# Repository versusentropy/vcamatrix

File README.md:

## eurorack 4x4 VCA matrix

revision v3.1
license CC-BY-SA-NC 4.0

46hp
355mA/325mA +/-12V

* signal input
  * full eurorack level (TODO scope pic)
  * passive normalized to input above
  * switch per column to normalize row 3&4 to 1&2 like a stereo pair
* 0-5V CV linear control
  * normalized to the CV above 
  * pre-/post knob switch between rows 1→2 and 3→4 
    * for stereo or main & send-fx 
    * 2→3 fixed pre
* dedicated output for each VCA
* mix output per VCA, that sums to the right, if nothing is plugged in
  * pin-headers on the back to chain multiple modules

Nobody ane would try to assemble the SMT parts by hand.
All SMT have a LCSC column for JLCPCB. For resistors all thin-film resistors <1% with the same package should be fine.  

## THT parts assembly

### BOM

* 1x 2x5 2.54mm shrouded pin header
  * power connector
* 2x 667-EEU-FR1V680H
  * electrolytic THT capacitor at power input (CP_Radial_D6.3mm_P2.50mm) 
* 1x 5k Trimmer 
  * Mouser 652-3296W-1-502LF
* 8x 2pin 2.54mm pin header
* 16x LED
  * Mouser 696-SSL-LX3044LYD
  * red version of same LED might work
  * other LEDs will most likely need different resistors.
* 8x Sub-Miniature Switch SPDT
* 4x Sub-Miniature DPDT

### Steps

**I recommend to do it EXACTLY 100% IN THIS ORDER WITHOUT COMBINING OR SKIPPING ANY STEPS.** 
I tried different processes. Many come with unexpected annoyances or take much longer without benefit. 
Place jacks means place jacks and nothing else!

#### 1
Place and solder 2.54mm pin headers at a right angle flush to the PCB. Solder 1pin, check & fix, finish.

* 4x 2pin 2.54mm pin header (green)
  * **These can not be installed later**, because the jacks will block the other side!
* 4x 2pin 2.54mm pin header (red)
  * These could be soldered to a finished module. But I recommend to solder them, even if you don't want to chain multiple modules. They help with placing jacks by holding up the PCB.

#### 2
Place and solder the power header

* 2x5 2.54mm shrouded pin header
  * **the notch must match the marking on the PCB!**
  * flush to the pcb to prevent damage when plugging in
    * solder 1pin, check & fix, finish

#### 3

Place and solder the offset trimmer

* 5k 3296W-1-502LF Trimmer
  * flush to the pcb to prevent damage when calibrating
    * solder 1pin, check & fix, finish

#### 4

Place all jacks. The loose leg goes into the square hole. Put it in first, then the next pin. Then third pin should go in easily. 
It's no problem, if 2 loose legs from the square pads of a neighboring jacks touch on the back, because that is the GND pin. Jacks are placed such, that the GND pads of 2 adjacent jacks always pair up.

#### 5

**Read the whole step, then** put on the front panel screw the 4 jacks at the corners and the 2 in the middle (5V and ∑) **FLUSH TO THE PANEL**.

 * Once the panel is put on, 
 * before and after screwing jacks in, 
 * until they have been soldered,
   * The panel
   * or the pcb
     * will tilt down on the side of the pots and rip out a few jacks.
     * then you have to remove the panel, which will pull out more jacks.
       * and you have to start over
         * that's why **YOU MUST NOT STOP HOLDING THE PCB AND THE PANEL TOGETHER UNTIL YOU ARE DONE!**
         * once the screws are tightened **JACK FLUSH TO THE PANEL**, flip everything into your positon for soldering
           * **WHILE HOLDING EVERYTHING TOGETHER!** put some weight near the ∑ to keep everything together.
 * **EVEN ONCE ALL JACKS ARE SOLDERED** 
   * **YOU MUST NOT REST YOU HAND** 
   * **OR PUT ANYTHING ELSE**
     * **ON THE POTS' SIDE OF**
       * **THE PCB**
       * **OR THE PANEL**
         * until much later, when the pots are placed
           * **OR YOU RISK TO BEND AND DAMAGE THE PCB**!
 * solder jacks with screws **while pressing the pcb down until the solder hardened! Do not proceed, if a jack isn't flush with the pcb.**
   * start with ∑
   * then 5V
   * then the 4 corners
 * now the risk of pulling out jacks is gone. 
 * **KEEP BEING CAREFUL NOT TO BEND THE PCB. DO NOT PUT PRESSURE ON EITHER SIDE WHERE THE POTS ARE MISSING!**

#### 6
 * verify, that all jacks sit flush with the pcb and the panel.
 * only then solder all remaining jacks
   * be careful not to solder one of the empty holes for the switches in the middle row by accident.
   * work from jack by jack and only solder a jack, if all 3 pins are properly inserted. Single improperly placed jacks should be soldered with the pots later.
 * verify, that all jacks sit flush with the pcb and the panel.
 * unscrew and remove panel

#### 7

Place and solder capacitors next to the power header.

* 2x 667-EEU-FR1V680H

#### 8

Place on the front side

 * 16x Pots
   * no metal tab at the pot
   * 1 washer
 * 4x DPDT switch between jacks
   * with 1 screw
   * all switches in same position (because it's easier to get the panel on)
 * 8x SPDT switch between pots
   * with 1 screw
   * all switches in same position (because it's easier to get the panel on)

#### 9
Place pcb on a box like in the photo, so LEDs' legs can dangle below.
 * 16x LED
   * Long leg into round hole
   * Must not stick out above the panel, until the panel is screwed to the other parts!

#### 10
Putting on the panel is a bit tricky. Do not use any force!
Panel and pcb should stay close to parallel, but getting in the switches needs some tilting.  

* LEDs should be out of the way at the bottom
* **do not tilt or bump, until all switches are through their holes**
  * or the switches fall over
    * and you might have to start over
* pots go first
  * if pcb and panel are at an angle, they won't go in easily. pulling the stuck panel back can pull a pot from the pcb. 
    * and you might have to start over 
* switches
  * one by one, from one end to the other
    * lowering the panel at a very slight angle
  * use tweezers to help them in
    * don't tip them over

#### 11

 * Verify pcb and panel are parallel
 * Screw all jacks flush
   * careful not to bend the pcb. pots should move in place
 * Verify pcb and panel are parallel
 * Screw pots flush to the panel
   * pot should lift slightly from the pcb (its pins will still stick out properly)
   * MAKE SURE NOT TO BEND THE PCB, when a pot sits a bit tight with its pins.
     * do others first
     * wiggle
 * Verify pcb and panel are parallel
 * Turn over for soldering without losing the LEDs
 * Solder pots
 * Screw switches flush to the panel
   * pins should barely stick out.

 * Turn over for soldering
 * Move LEDs into holes
 * Solder switches
   * make sure to heat pad and pin even, if the pin barely sticks out
 * Solder LEDs one by one while module is (close to) vertical
   * adjust LED to panel 
   * solder short leg first
   * check alignment
   * grab front and long leg with one hand
   * reheat round pad and adjust
   * solder 2nd pin and cut legs

#### 12

To check for shorts before powering up measure across the small SMT capacitors near the power header, that are connected to the electrolytic caps via big copper planes.

* positive side
* negative side
* positive (+ of electrolytic) to negative (- of electrolytic)

Trimmer should be set such, that
* VCAs are fully closed when their knob is set fully counter-clockwise.
* when properly set, there should be no bleed.

TODO add scope pics

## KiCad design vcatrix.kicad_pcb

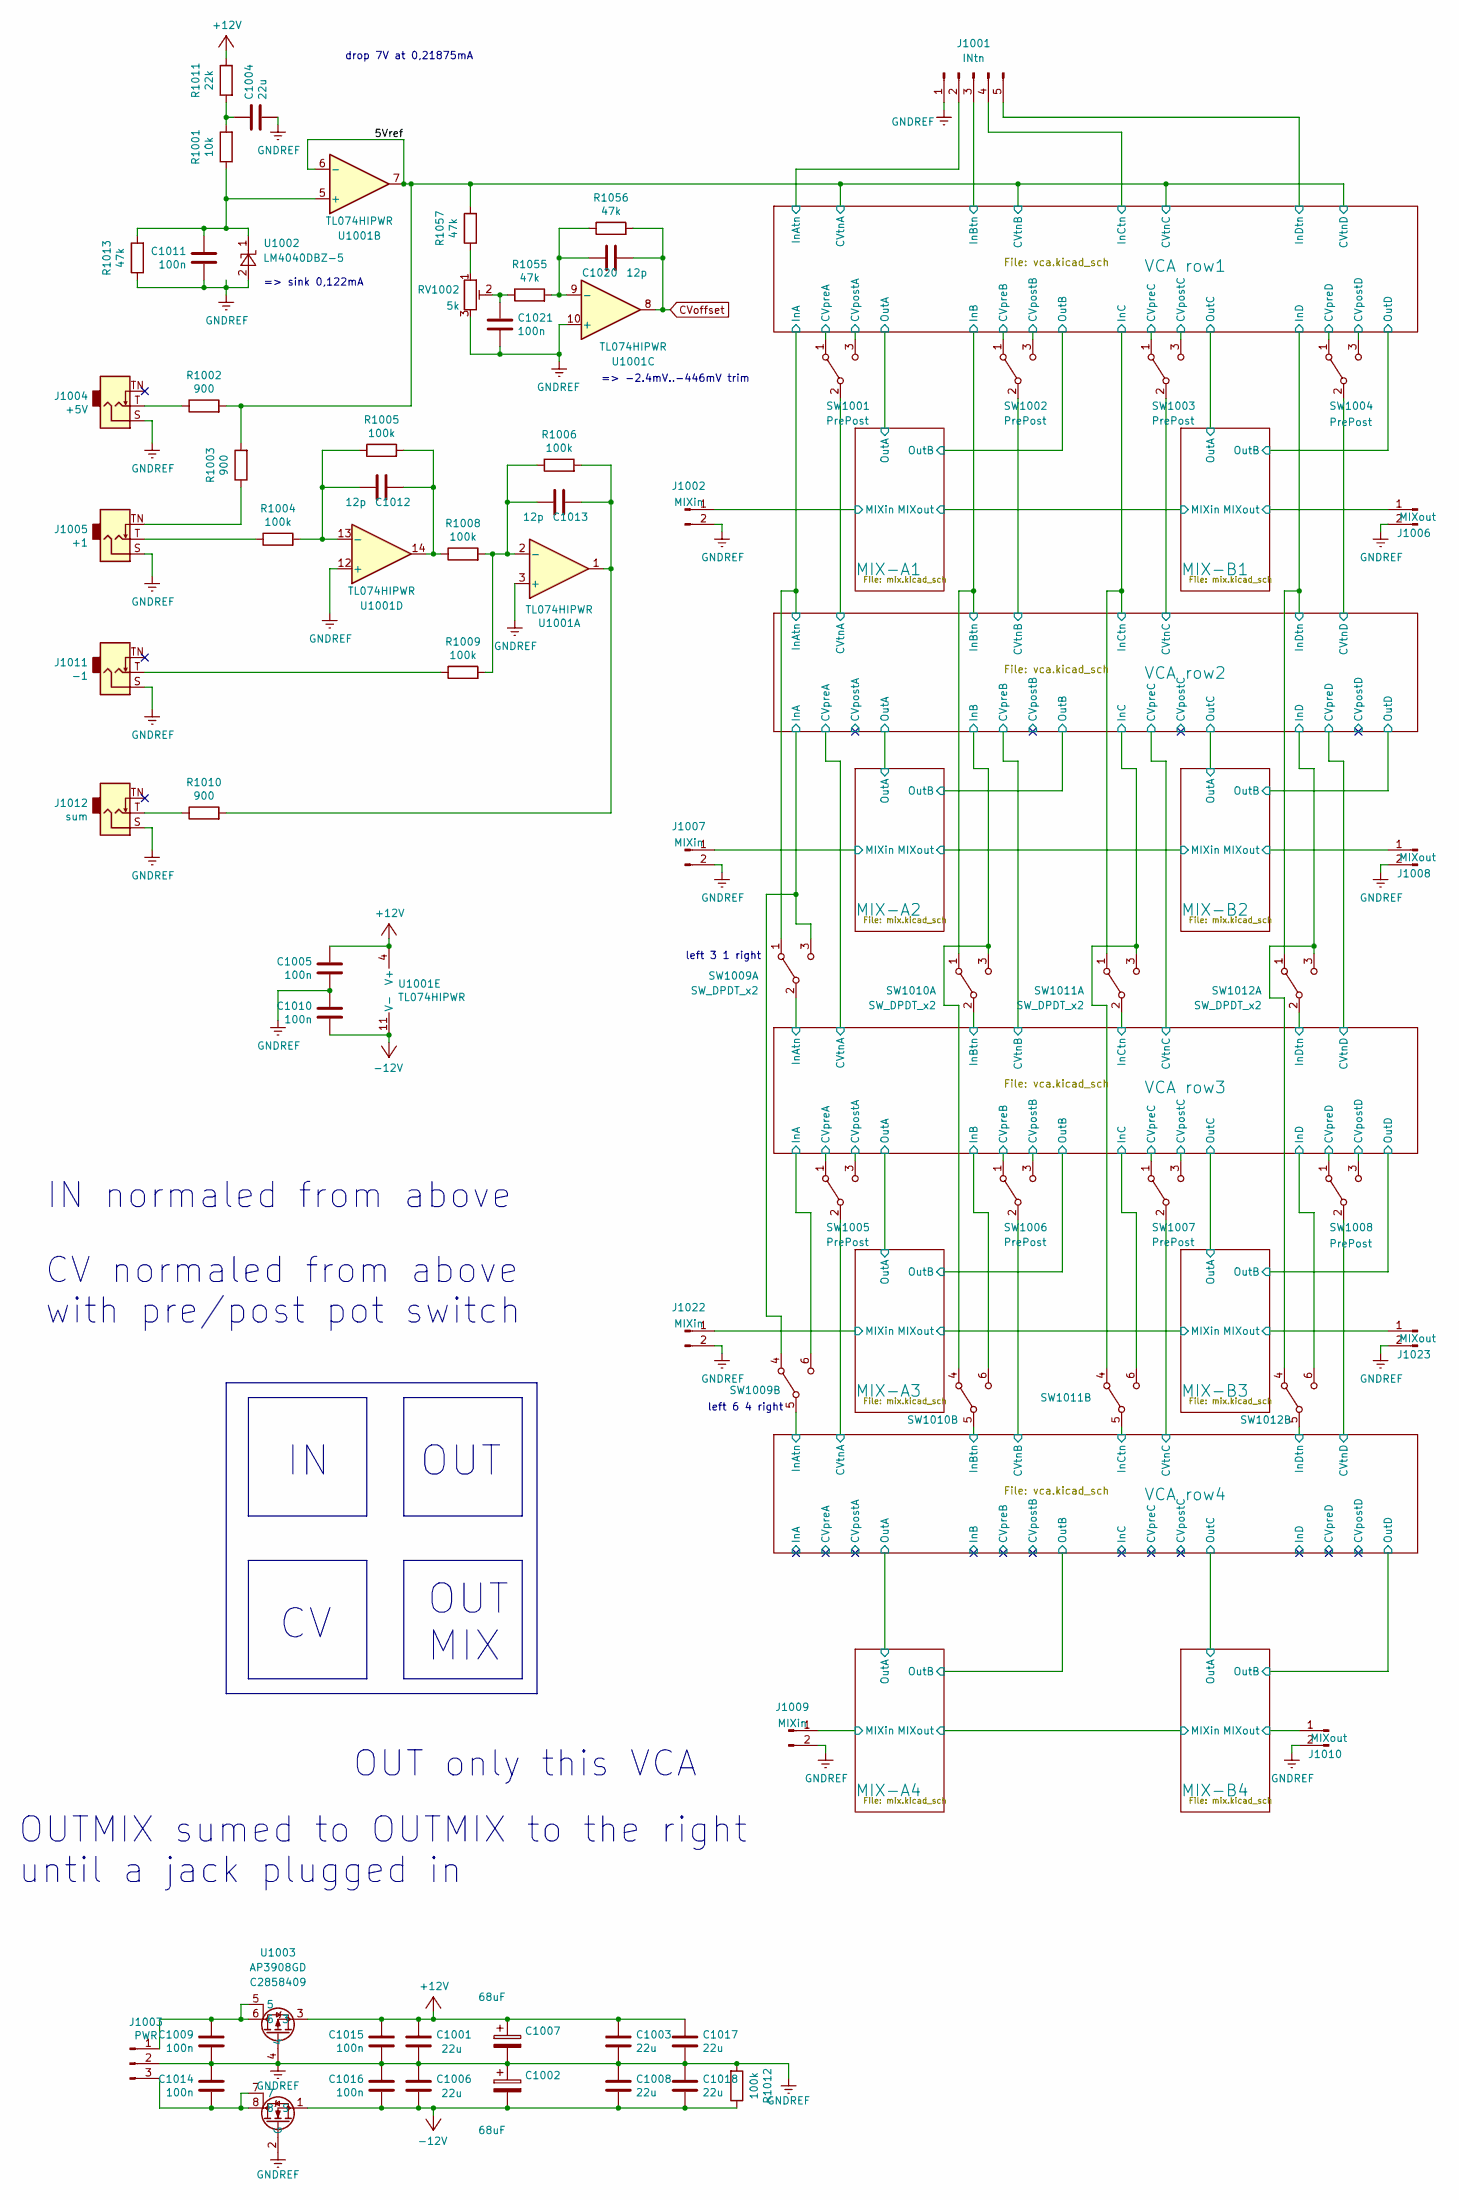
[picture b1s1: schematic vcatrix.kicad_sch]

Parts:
C1001, C1003, C1004, C1006, C1008, C1017, C1018: 22u; C_0805_2012Metric; LCSC C86816
C1002, C1007: 68uF; CP_Radial_D6.3mm_P2.50mm; Mouser 667-EEU-FR1V680H
C1005, C1009, C1010, C1011, C1014, C1015, C1016, C1021: 100n; C_0402_1005Metric; LCSC C307331
C1012, C1013, C1020: 12p; C_0402_1005Metric; LCSC C1547
J1001: INtn; PinHeader_1x05_P2.54mm_Vertical
J1002, J1007, J1009, J1022: MIXin; PinHeader_1x02_P2.54mm_Vertical
J1003: PWR; eurorac_power-v2; Mouser 737-BHR-10-VUA
J1004: +5V; Jack_3.5mm_QingPu_WQP-PJ398SM_Vertical_CircularHolesSMALL
J1005: +1; Jack_3.5mm_QingPu_WQP-PJ398SM_Vertical_CircularHolesSMALL
J1006, J1008, J1010, J1023: MIXout; PinHeader_1x02_P2.54mm_Vertical
J1011: -1; Jack_3.5mm_QingPu_WQP-PJ398SM_Vertical_CircularHolesSMALL
J1012: sum; Jack_3.5mm_QingPu_WQP-PJ398SM_Vertical_CircularHolesSMALL
R1001: 10k; R_0402_1005Metric; LCSC C190095
R1002, R1003, R1010: 900; R_0603_1608Metric; LCSC C3013565
R1004, R1005, R1006, R1008, R1009, R1012: 100k; R_0402_1005Metric; LCSC C317929
R1011: 22k; R_0402_1005Metric; LCSC C25768
R1013, R1055, R1056, R1057: 47k; R_0402_1005Metric; LCSC C358418
RV1002: 5k; Potentiometer_Bourns_3296W_Vertical; Mouser 652-3296W-1-502LF
SW1001, SW1002, SW1003, SW1004, SW1005, SW1006, SW1007, SW1008: PrePost; SW_SPDT_2_5mm
SW1009, SW1010, SW1011, SW1012: SW_DPDT_x2; SW_DPDT_2_5mm
U1001: TL074HIPWR; TSSOP-14_4.4x5mm_P0.65mm; LCSC C4370424
U1002: LM4040DBZ-5; SOT-23; LCSC C460606
U1003: AP3908GD; LCSC C2858409

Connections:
+12V: C1001.1, C1003.1, C1005.2, C1007.1, C1015.2, C1017.1, R1011.1, U1001.4 (V+), U1003.3; also elsewhere on the board
-12V: C1002.2, C1006.2, C1008.2, C1010.1, C1016.1, C1018.2, R1012.1, U1001.11 (V-), U1003.1 (S); also elsewhere on the board
/5Vref: R1002.2, R1003.2, R1057.2, U1001.6 (-), U1001.7; also elsewhere on the board
/MIX-A1/MIXin: J1002.1; also elsewhere on the board
/MIX-A2/MIXin: J1007.1; also elsewhere on the board
/MIX-A3/MIXin: J1022.1; also elsewhere on the board
/MIX-A4/MIXin: J1009.1; also elsewhere on the board
/MIX-B1/MIXout: J1006.1; also elsewhere on the board
/MIX-B2/MIXout: J1008.1; also elsewhere on the board
/MIX-B3/MIXout: J1023.1; also elsewhere on the board
/MIX-B4/MIXout: J1010.1; also elsewhere on the board
/VCA row1/CVpostA: SW1001.3 (C); also elsewhere on the board
/VCA row1/CVpostB: SW1002.3 (C); also elsewhere on the board
/VCA row1/CVpostC: SW1003.3 (C); also elsewhere on the board
/VCA row1/CVpostD: SW1004.3 (C); also elsewhere on the board
/VCA row1/CVpreA: SW1001.1 (A); also elsewhere on the board
/VCA row1/CVpreB: SW1002.1 (A); also elsewhere on the board
/VCA row1/CVpreC: SW1003.1 (A); also elsewhere on the board
/VCA row1/CVpreD: SW1004.1 (A); also elsewhere on the board
/VCA row1/InA: SW1009.1 (A); also elsewhere on the board
/VCA row1/InAtn: J1001.2; also elsewhere on the board
/VCA row1/InB: SW1010.1 (A); also elsewhere on the board
/VCA row1/InBtn: J1001.3; also elsewhere on the board
/VCA row1/InC: SW1011.1 (A); also elsewhere on the board
/VCA row1/InCtn: J1001.4; also elsewhere on the board
/VCA row1/InD: SW1012.1 (A); also elsewhere on the board
/VCA row1/InDtn: J1001.5; also elsewhere on the board
/VCA row2/CVtnA: SW1001.2 (B); also elsewhere on the board
/VCA row2/CVtnB: SW1002.2 (B); also elsewhere on the board
/VCA row2/CVtnC: SW1003.2 (B); also elsewhere on the board
/VCA row2/CVtnD: SW1004.2 (B); also elsewhere on the board
/VCA row2/InA: SW1009.3 (C), SW1009.4 (A); also elsewhere on the board
/VCA row2/InB: SW1010.3 (C), SW1010.4 (A); also elsewhere on the board
/VCA row2/InC: SW1011.3 (C), SW1011.4 (A); also elsewhere on the board
/VCA row2/InD: SW1012.3 (C), SW1012.4 (A); also elsewhere on the board
/VCA row3/CVpostA: SW1005.3 (C); also elsewhere on the board
/VCA row3/CVpostB: SW1006.3 (C); also elsewhere on the board
/VCA row3/CVpostC: SW1007.3 (C); also elsewhere on the board
/VCA row3/CVpostD: SW1008.3 (C); also elsewhere on the board
/VCA row3/CVpreA: SW1005.1 (A); also elsewhere on the board
/VCA row3/CVpreB: SW1006.1 (A); also elsewhere on the board
/VCA row3/CVpreC: SW1007.1 (A); also elsewhere on the board
/VCA row3/CVpreD: SW1008.1 (A); also elsewhere on the board
/VCA row3/InA: SW1009.6 (C); also elsewhere on the board
/VCA row3/InAtn: SW1009.2 (B); also elsewhere on the board
/VCA row3/InB: SW1010.6 (C); also elsewhere on the board
/VCA row3/InBtn: SW1010.2 (B); also elsewhere on the board
/VCA row3/InC: SW1011.6 (C); also elsewhere on the board
/VCA row3/InCtn: SW1011.2 (B); also elsewhere on the board
/VCA row3/InD: SW1012.6 (C); also elsewhere on the board
/VCA row3/InDtn: SW1012.2 (B); also elsewhere on the board
/VCA row4/CVtnA: SW1005.2 (B); also elsewhere on the board
/VCA row4/CVtnB: SW1006.2 (B); also elsewhere on the board
/VCA row4/CVtnC: SW1007.2 (B); also elsewhere on the board
/VCA row4/CVtnD: SW1008.2 (B); also elsewhere on the board
/VCA row4/InAtn: SW1009.5 (B); also elsewhere on the board
/VCA row4/InBtn: SW1010.5 (B); also elsewhere on the board
/VCA row4/InCtn: SW1011.5 (B); also elsewhere on the board
/VCA row4/InDtn: SW1012.5 (B); also elsewhere on the board
CVoffset: C1020.2, R1056.2, U1001.8; also elsewhere on the board
GNDREF: C1001.2, C1002.1, C1003.2, C1004.2, C1005.1, C1006.1, C1007.2, C1008.1, C1009.1, C1010.2, C1011.1, C1014.2, C1015.1, C1016.2, C1017.2, C1018.1, C1021.1, J1001.1, J1002.2, J1003.2, J1004.S, J1005.S, J1006.2, J1007.2, J1008.2, J1009.2, J1010.2, J1011.S, J1012.S, J1022.2, J1023.2, R1012.2, R1013.1, RV1002.3, U1001.3 (+), U1001.10 (+), U1001.12 (+), U1002.2 (A), U1003.2 (G), U1003.4; also elsewhere on the board
unnamed: C1004.1, R1001.2, R1011.2
unnamed: C1012.1, R1005.2, R1008.1, U1001.14
unnamed: C1013.1, R1006.2, R1010.2, U1001.1
unnamed: C1021.2, R1055.1, RV1002.2
unnamed: C1009.2, J1003.1, U1003.5, U1003.6
unnamed: C1014.1, J1003.3, U1003.7, U1003.8
unnamed: J1004.T, R1002.1
unnamed: J1005.T, R1004.1
unnamed: J1005.TN, R1003.1
unnamed: J1011.T, R1009.1
unnamed: J1012.T, R1010.1
unnamed: R1057.1, RV1002.1
unnamed: C1013.2, R1006.1, R1008.2, R1009.2, U1001.2 (-)
unnamed: C1011.2, R1001.1, R1013.2, U1001.5 (+), U1002.1 (K)
unnamed: C1020.1, R1055.2, R1056.1, U1001.9 (-)
unnamed: C1012.2, R1004.2, R1005.1, U1001.13 (-)

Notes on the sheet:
left 3 1 right
OUTMIX sumed to OUTMIX to the right until a jack plugged in
OUT only this VCA
CV normaled from above with pre/post pot switch
drop 7V at 0,21875mA
=> -2.4mV..-446mV trim
OUT MIX
left 6 4 right
OUT
IN normaled from above
=> sink 0,122mA

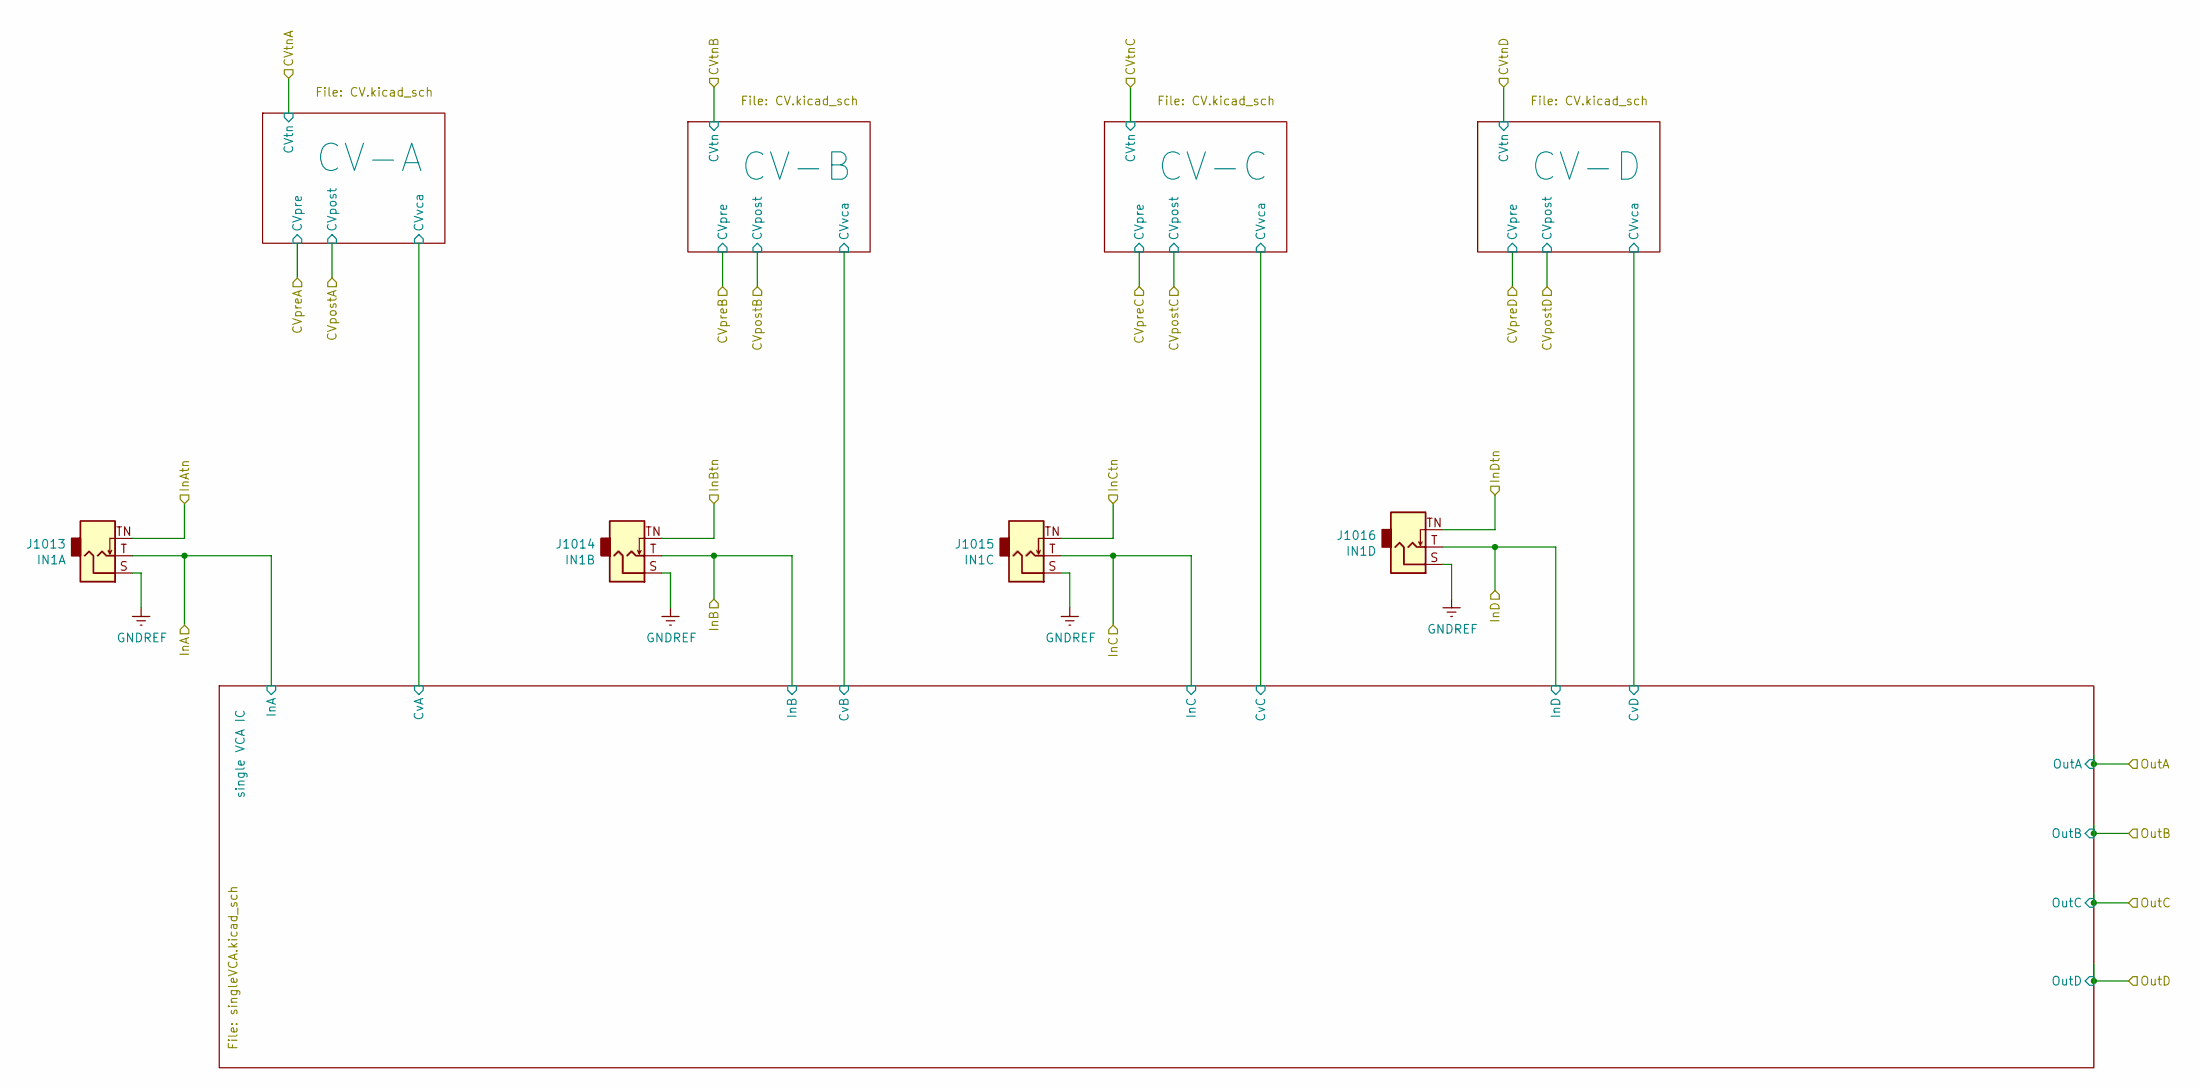
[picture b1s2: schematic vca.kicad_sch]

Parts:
J1013: IN1A; Jack_3.5mm_QingPu_WQP-PJ398SM_Vertical_CircularHolesSMALL
J1014: IN1B; Jack_3.5mm_QingPu_WQP-PJ398SM_Vertical_CircularHolesSMALL
J1015: IN1C; Jack_3.5mm_QingPu_WQP-PJ398SM_Vertical_CircularHolesSMALL
J1016: IN1D; Jack_3.5mm_QingPu_WQP-PJ398SM_Vertical_CircularHolesSMALL

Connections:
/VCA row1/InA: J1013.T; also elsewhere on the board
/VCA row1/InAtn: J1013.TN; also elsewhere on the board
/VCA row1/InB: J1014.T; also elsewhere on the board
/VCA row1/InBtn: J1014.TN; also elsewhere on the board
/VCA row1/InC: J1015.T; also elsewhere on the board
/VCA row1/InCtn: J1015.TN; also elsewhere on the board
/VCA row1/InD: J1016.T; also elsewhere on the board
/VCA row1/InDtn: J1016.TN; also elsewhere on the board
GNDREF: J1013.S, J1014.S, J1015.S, J1016.S; also elsewhere on the board

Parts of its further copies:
J2401, J3401, J4401: IN1D; Jack_3.5mm_QingPu_WQP-PJ398SM_Vertical_CircularHolesSMALL
J2402, J3402, J4402: IN1A; Jack_3.5mm_QingPu_WQP-PJ398SM_Vertical_CircularHolesSMALL
J2403, J3403, J4403: IN1B; Jack_3.5mm_QingPu_WQP-PJ398SM_Vertical_CircularHolesSMALL
J2404, J3404, J4404: IN1C; Jack_3.5mm_QingPu_WQP-PJ398SM_Vertical_CircularHolesSMALL

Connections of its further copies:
/VCA row1/InA: J2402.TN; also elsewhere on the board
/VCA row1/InB: J2403.TN; also elsewhere on the board
/VCA row1/InC: J2404.TN; also elsewhere on the board
/VCA row1/InD: J2401.TN; also elsewhere on the board
/VCA row2/InA: J2402.T; also elsewhere on the board
/VCA row2/InB: J2403.T; also elsewhere on the board
/VCA row2/InC: J2404.T; also elsewhere on the board
/VCA row2/InD: J2401.T; also elsewhere on the board
/VCA row3/InA: J3402.T; also elsewhere on the board
/VCA row3/InAtn: J3402.TN; also elsewhere on the board
/VCA row3/InB: J3403.T; also elsewhere on the board
/VCA row3/InBtn: J3403.TN; also elsewhere on the board
/VCA row3/InC: J3404.T; also elsewhere on the board
/VCA row3/InCtn: J3404.TN; also elsewhere on the board
/VCA row3/InD: J3401.T; also elsewhere on the board
/VCA row3/InDtn: J3401.TN; also elsewhere on the board
/VCA row4/InA: J4402.T; also elsewhere on the board
/VCA row4/InAtn: J4402.TN; also elsewhere on the board
/VCA row4/InB: J4403.T; also elsewhere on the board
/VCA row4/InBtn: J4403.TN; also elsewhere on the board
/VCA row4/InC: J4404.T; also elsewhere on the board
/VCA row4/InCtn: J4404.TN; also elsewhere on the board
/VCA row4/InD: J4401.T; also elsewhere on the board
/VCA row4/InDtn: J4401.TN; also elsewhere on the board
GNDREF: J2401.S, J2402.S, J2403.S, J2404.S, J3401.S, J3402.S, J3403.S, J3404.S, J4401.S, J4402.S, J4403.S, J4404.S; also elsewhere on the board

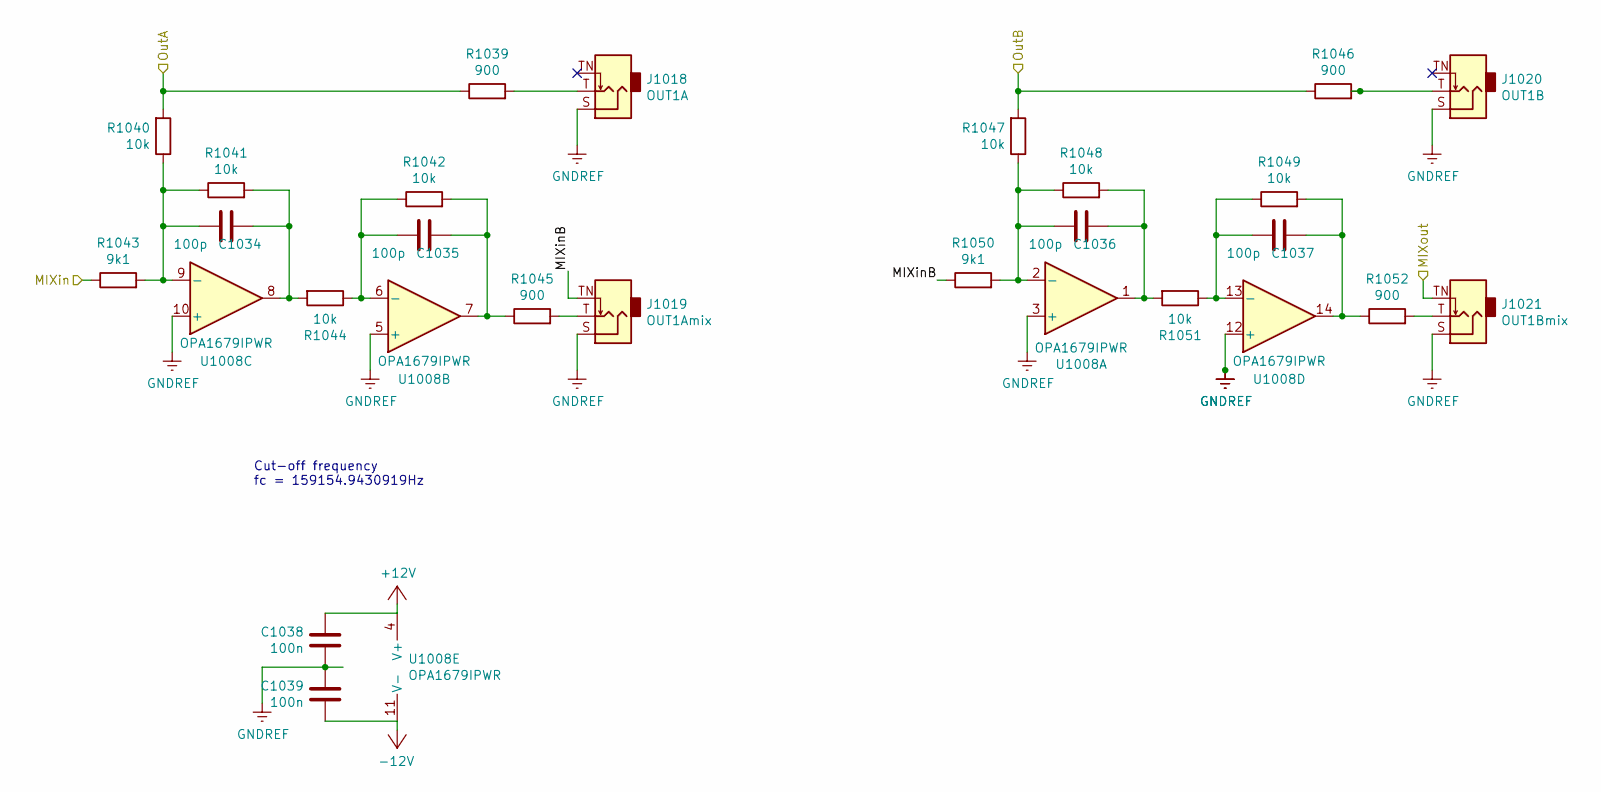
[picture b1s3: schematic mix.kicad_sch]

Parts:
C1034, C1035, C1036, C1037: 100p; C_0402_1005Metric; LCSC C1546
C1038, C1039: 100n; C_0402_1005Metric; LCSC C307331
J1018: OUT1A; Jack_3.5mm_QingPu_WQP-PJ398SM_Vertical_CircularHolesSMALL
J1019: OUT1Amix; Jack_3.5mm_QingPu_WQP-PJ398SM_Vertical_CircularHolesSMALL
J1020: OUT1B; Jack_3.5mm_QingPu_WQP-PJ398SM_Vertical_CircularHolesSMALL
J1021: OUT1Bmix; Jack_3.5mm_QingPu_WQP-PJ398SM_Vertical_CircularHolesSMALL
R1039, R1045, R1046, R1052: 900; R_0603_1608Metric; LCSC C3013565
R1040, R1041, R1042, R1044, R1047, R1048, R1049, R1051: 10k; R_0402_1005Metric; LCSC C190095
R1043, R1050: 9k1; R_0603_1608Metric; LCSC C136945
U1008: OPA1679IPWR; TSSOP-14_4.4x5mm_P0.65mm; LCSC C2057264

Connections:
+12V: C1038.2, U1008.4 (V+); also elsewhere on the board
-12V: C1039.1, U1008.11 (V-); also elsewhere on the board
/MIX-A1/MIXin: R1043.1; also elsewhere on the board
/MIX-A1/MIXinB: J1019.TN, R1050.1
/MIX-A1/MIXout: J1021.TN; also elsewhere on the board
/MIX-A1/OutA: R1039.1, R1040.2; also elsewhere on the board
/MIX-A1/OutB: R1046.1, R1047.2; also elsewhere on the board
GNDREF: C1038.1, C1039.2, J1018.S, J1019.S, J1020.S, J1021.S, U1008.3 (+), U1008.5 (+), U1008.10 (+), U1008.12 (+); also elsewhere on the board
unnamed: C1034.1, R1041.2, R1044.2, U1008.8
unnamed: C1035.1, R1042.2, R1045.1, U1008.7
unnamed: C1036.1, R1048.2, R1051.2, U1008.1
unnamed: C1037.1, R1049.2, R1052.1, U1008.14
unnamed: J1018.T, R1039.2
unnamed: J1019.T, R1045.2
unnamed: J1020.T, R1046.2
unnamed: J1021.T, R1052.2
unnamed: C1036.2, R1047.1, R1048.1, R1050.2, U1008.2 (-)
unnamed: C1035.2, R1042.1, R1044.1, U1008.6 (-)
unnamed: C1034.2, R1040.1, R1041.1, R1043.2, U1008.9 (-)
unnamed: C1037.2, R1049.1, R1051.1, U1008.13 (-)

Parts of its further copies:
C2601, C2602, C2603, C2604, C2701, C2702, C2703, C2704, C2801, C2802, C2803, C2804, C3601, C3602, C3603, C3604, C3701, C3702, C3703, C3704, C4601, C4602, C4603, C4604, C4701, C4702, C4703, C4704: 100p; C_0402_1005Metric; LCSC C1546
C2605, C2606, C2705, C2706, C2805, C2806, C3605, C3606, C3705, C3706, C4605, C4606, C4705, C4706: 100n; C_0402_1005Metric; LCSC C307331
J2601, J2701, J2801, J3601, J3701, J4601, J4701: OUT1A; Jack_3.5mm_QingPu_WQP-PJ398SM_Vertical_CircularHolesSMALL
J2602, J2702, J2802, J3602, J3702, J4602, J4702: OUT1B; Jack_3.5mm_QingPu_WQP-PJ398SM_Vertical_CircularHolesSMALL
J2603, J2703, J2803, J3603, J3703, J4603, J4703: OUT1Amix; Jack_3.5mm_QingPu_WQP-PJ398SM_Vertical_CircularHolesSMALL
J2604, J2704, J2804, J3604, J3704, J4604, J4704: OUT1Bmix; Jack_3.5mm_QingPu_WQP-PJ398SM_Vertical_CircularHolesSMALL
R2601, R2602, R2613, R2614, R2701, R2702, R2713, R2714, R2801, R2802, R2813, R2814, R3601, R3602, R3613, R3614, R3701, R3702, R3713, R3714, R4601, R4602, R4613, R4614, R4701, R4702, R4713, R4714: 900; R_0603_1608Metric; LCSC C3013565
R2603, R2604, R2605, R2606, R2607, R2608, R2611, R2612, R2703, R2704, R2705, R2706, R2707, R2708, R2711, R2712, R2803, R2804, R2805, R2806, R2807, R2808, R2811, R2812, R3603, R3604, R3605, R3606, R3607, R3608, R3611, R3612, R3703, R3704, R3705, R3706, R3707, R3708, R3711, R3712, R4603, R4604, R4605, R4606, R4607, R4608, R4611, R4612, R4703, R4704, R4705, R4706, R4707, R4708, R4711, R4712: 10k; R_0402_1005Metric; LCSC C190095
R2609, R2610, R2709, R2710, R2809, R2810, R3609, R3610, R3709, R3710, R4609, R4610, R4709, R4710: 9k1; R_0603_1608Metric; LCSC C136945
U2601, U2701, U2801, U3601, U3701, U4601, U4701: OPA1679IPWR; TSSOP-14_4.4x5mm_P0.65mm; LCSC C2057264

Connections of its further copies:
+12V: C2605.2, C2705.2, C2805.2, C3605.2, C3705.2, C4605.2, C4705.2, U2601.4 (V+), U2701.4 (V+), U2801.4 (V+), U3601.4 (V+), U3701.4 (V+), U4601.4 (V+), U4701.4 (V+); also elsewhere on the board
-12V: C2606.1, C2706.1, C2806.1, C3606.1, C3706.1, C4606.1, C4706.1, U2601.11 (V-), U2701.11 (V-), U2801.11 (V-), U3601.11 (V-), U3701.11 (V-), U4601.11 (V-), U4701.11 (V-); also elsewhere on the board
/MIX-A1/MIXout: R2609.1; also elsewhere on the board
/MIX-A2/MIXin: R2709.1; also elsewhere on the board
/MIX-A2/MIXinB: J2703.TN, R2710.1
/MIX-A2/MIXout: J2704.TN, R2809.1
/MIX-A2/OutA: R2701.1, R2703.2; also elsewhere on the board
/MIX-A2/OutB: R2702.1, R2704.2; also elsewhere on the board
/MIX-A3/MIXin: R3609.1; also elsewhere on the board
/MIX-A3/MIXinB: J3603.TN, R3610.1
/MIX-A3/MIXout: J3604.TN, R3709.1
/MIX-A3/OutA: R3601.1, R3603.2; also elsewhere on the board
/MIX-A3/OutB: R3602.1, R3604.2; also elsewhere on the board
/MIX-A4/MIXin: R4609.1; also elsewhere on the board
/MIX-A4/MIXinB: J4603.TN, R4610.1
/MIX-A4/MIXout: J4604.TN, R4709.1
/MIX-A4/OutA: R4601.1, R4603.2; also elsewhere on the board
/MIX-A4/OutB: R4602.1, R4604.2; also elsewhere on the board
/MIX-B1/MIXinB: J2603.TN, R2610.1
/MIX-B1/MIXout: J2604.TN; also elsewhere on the board
/MIX-B1/OutA: R2601.1, R2603.2; also elsewhere on the board
/MIX-B1/OutB: R2602.1, R2604.2; also elsewhere on the board
/MIX-B2/MIXinB: J2803.TN, R2810.1
/MIX-B2/MIXout: J2804.TN; also elsewhere on the board
/MIX-B2/OutA: R2801.1, R2803.2; also elsewhere on the board
/MIX-B2/OutB: R2802.1, R2804.2; also elsewhere on the board
/MIX-B3/MIXinB: J3703.TN, R3710.1
/MIX-B3/MIXout: J3704.TN; also elsewhere on the board
/MIX-B3/OutA: R3701.1, R3703.2; also elsewhere on the board
/MIX-B3/OutB: R3702.1, R3704.2; also elsewhere on the board
/MIX-B4/MIXinB: J4703.TN, R4710.1
/MIX-B4/MIXout: J4704.TN; also elsewhere on the board
/MIX-B4/OutA: R4701.1, R4703.2; also elsewhere on the board
/MIX-B4/OutB: R4702.1, R4704.2; also elsewhere on the board
GNDREF: C2605.1, C2606.2, C2705.1, C2706.2, C2805.1, C2806.2, C3605.1, C3606.2, C3705.1, C3706.2, C4605.1, C4606.2, C4705.1, C4706.2, J2601.S, J2602.S, J2603.S, J2604.S, J2701.S, J2702.S, J2703.S, J2704.S, J2801.S, J2802.S, J2803.S, J2804.S, J3601.S, J3602.S, J3603.S, J3604.S, J3701.S, J3702.S, J3703.S, J3704.S, J4601.S, J4602.S, J4603.S, J4604.S, J4701.S, J4702.S, J4703.S, J4704.S, U2601.3 (+), U2601.5 (+), U2601.10 (+), U2601.12 (+), U2701.3 (+), U2701.5 (+), U2701.10 (+), U2701.12 (+), U2801.3 (+), U2801.5 (+), U2801.10 (+), U2801.12 (+), U3601.3 (+), U3601.5 (+), U3601.10 (+), U3601.12 (+), U3701.3 (+), U3701.5 (+), U3701.10 (+), U3701.12 (+), U4601.3 (+), U4601.5 (+), U4601.10 (+), U4601.12 (+), U4701.3 (+), U4701.5 (+), U4701.10 (+), U4701.12 (+); also elsewhere on the board
unnamed: C2601.1, R2605.2, R2611.2, U2601.8
unnamed: C2602.1, R2606.2, R2612.2, U2601.1
unnamed: C2603.1, R2607.2, R2613.1, U2601.7
unnamed: C2604.1, R2608.2, R2614.1, U2601.14
unnamed: C2701.1, R2705.2, R2711.2, U2701.8
unnamed: C2702.1, R2706.2, R2712.2, U2701.1
unnamed: C2703.1, R2707.2, R2713.1, U2701.7
unnamed: C2704.1, R2708.2, R2714.1, U2701.14
unnamed: C2801.1, R2805.2, R2811.2, U2801.8
unnamed: C2802.1, R2806.2, R2812.2, U2801.1
unnamed: C2803.1, R2807.2, R2813.1, U2801.7
unnamed: C2804.1, R2808.2, R2814.1, U2801.14
unnamed: C3601.1, R3605.2, R3611.2, U3601.8
unnamed: C3602.1, R3606.2, R3612.2, U3601.1
unnamed: C3603.1, R3607.2, R3613.1, U3601.7
unnamed: C3604.1, R3608.2, R3614.1, U3601.14
unnamed: C3701.1, R3705.2, R3711.2, U3701.8
unnamed: C3702.1, R3706.2, R3712.2, U3701.1
unnamed: C3703.1, R3707.2, R3713.1, U3701.7
unnamed: C3704.1, R3708.2, R3714.1, U3701.14
unnamed: C4601.1, R4605.2, R4611.2, U4601.8
unnamed: C4602.1, R4606.2, R4612.2, U4601.1
unnamed: C4603.1, R4607.2, R4613.1, U4601.7
unnamed: C4604.1, R4608.2, R4614.1, U4601.14
unnamed: C4701.1, R4705.2, R4711.2, U4701.8
unnamed: C4702.1, R4706.2, R4712.2, U4701.1
unnamed: C4703.1, R4707.2, R4713.1, U4701.7
unnamed: C4704.1, R4708.2, R4714.1, U4701.14
unnamed: J2601.T, R2601.2
unnamed: J2602.T, R2602.2
unnamed: J2603.T, R2613.2
unnamed: J2604.T, R2614.2
unnamed: J2701.T, R2701.2
unnamed: J2702.T, R2702.2
unnamed: J2703.T, R2713.2
unnamed: J2704.T, R2714.2
unnamed: J2801.T, R2801.2
unnamed: J2802.T, R2802.2
unnamed: J2803.T, R2813.2
unnamed: J2804.T, R2814.2
unnamed: J3601.T, R3601.2
unnamed: J3602.T, R3602.2
unnamed: J3603.T, R3613.2
unnamed: J3604.T, R3614.2
unnamed: J3701.T, R3701.2
unnamed: J3702.T, R3702.2
unnamed: J3703.T, R3713.2
unnamed: J3704.T, R3714.2
unnamed: J4601.T, R4601.2
unnamed: J4602.T, R4602.2
unnamed: J4603.T, R4613.2
unnamed: J4604.T, R4614.2
unnamed: J4701.T, R4701.2
unnamed: J4702.T, R4702.2
unnamed: J4703.T, R4713.2
unnamed: J4704.T, R4714.2
unnamed: C2602.2, R2604.1, R2606.1, R2610.2, U2601.2 (-)
unnamed: C2603.2, R2607.1, R2611.1, U2601.6 (-)
unnamed: C2601.2, R2603.1, R2605.1, R2609.2, U2601.9 (-)
unnamed: C2604.2, R2608.1, R2612.1, U2601.13 (-)
unnamed: C2702.2, R2704.1, R2706.1, R2710.2, U2701.2 (-)
unnamed: C2703.2, R2707.1, R2711.1, U2701.6 (-)
unnamed: C2701.2, R2703.1, R2705.1, R2709.2, U2701.9 (-)
unnamed: C2704.2, R2708.1, R2712.1, U2701.13 (-)
unnamed: C2802.2, R2804.1, R2806.1, R2810.2, U2801.2 (-)
unnamed: C2803.2, R2807.1, R2811.1, U2801.6 (-)
unnamed: C2801.2, R2803.1, R2805.1, R2809.2, U2801.9 (-)
unnamed: C2804.2, R2808.1, R2812.1, U2801.13 (-)
unnamed: C3602.2, R3604.1, R3606.1, R3610.2, U3601.2 (-)
unnamed: C3603.2, R3607.1, R3611.1, U3601.6 (-)
unnamed: C3601.2, R3603.1, R3605.1, R3609.2, U3601.9 (-)
unnamed: C3604.2, R3608.1, R3612.1, U3601.13 (-)
unnamed: C3702.2, R3704.1, R3706.1, R3710.2, U3701.2 (-)
unnamed: C3703.2, R3707.1, R3711.1, U3701.6 (-)
unnamed: C3701.2, R3703.1, R3705.1, R3709.2, U3701.9 (-)
unnamed: C3704.2, R3708.1, R3712.1, U3701.13 (-)
unnamed: C4602.2, R4604.1, R4606.1, R4610.2, U4601.2 (-)
unnamed: C4603.2, R4607.1, R4611.1, U4601.6 (-)
unnamed: C4601.2, R4603.1, R4605.1, R4609.2, U4601.9 (-)
unnamed: C4604.2, R4608.1, R4612.1, U4601.13 (-)
unnamed: C4702.2, R4704.1, R4706.1, R4710.2, U4701.2 (-)
unnamed: C4703.2, R4707.1, R4711.1, U4701.6 (-)
unnamed: C4701.2, R4703.1, R4705.1, R4709.2, U4701.9 (-)
unnamed: C4704.2, R4708.1, R4712.1, U4701.13 (-)

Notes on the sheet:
Cut-off frequency fc = 159154.9430919Hz
